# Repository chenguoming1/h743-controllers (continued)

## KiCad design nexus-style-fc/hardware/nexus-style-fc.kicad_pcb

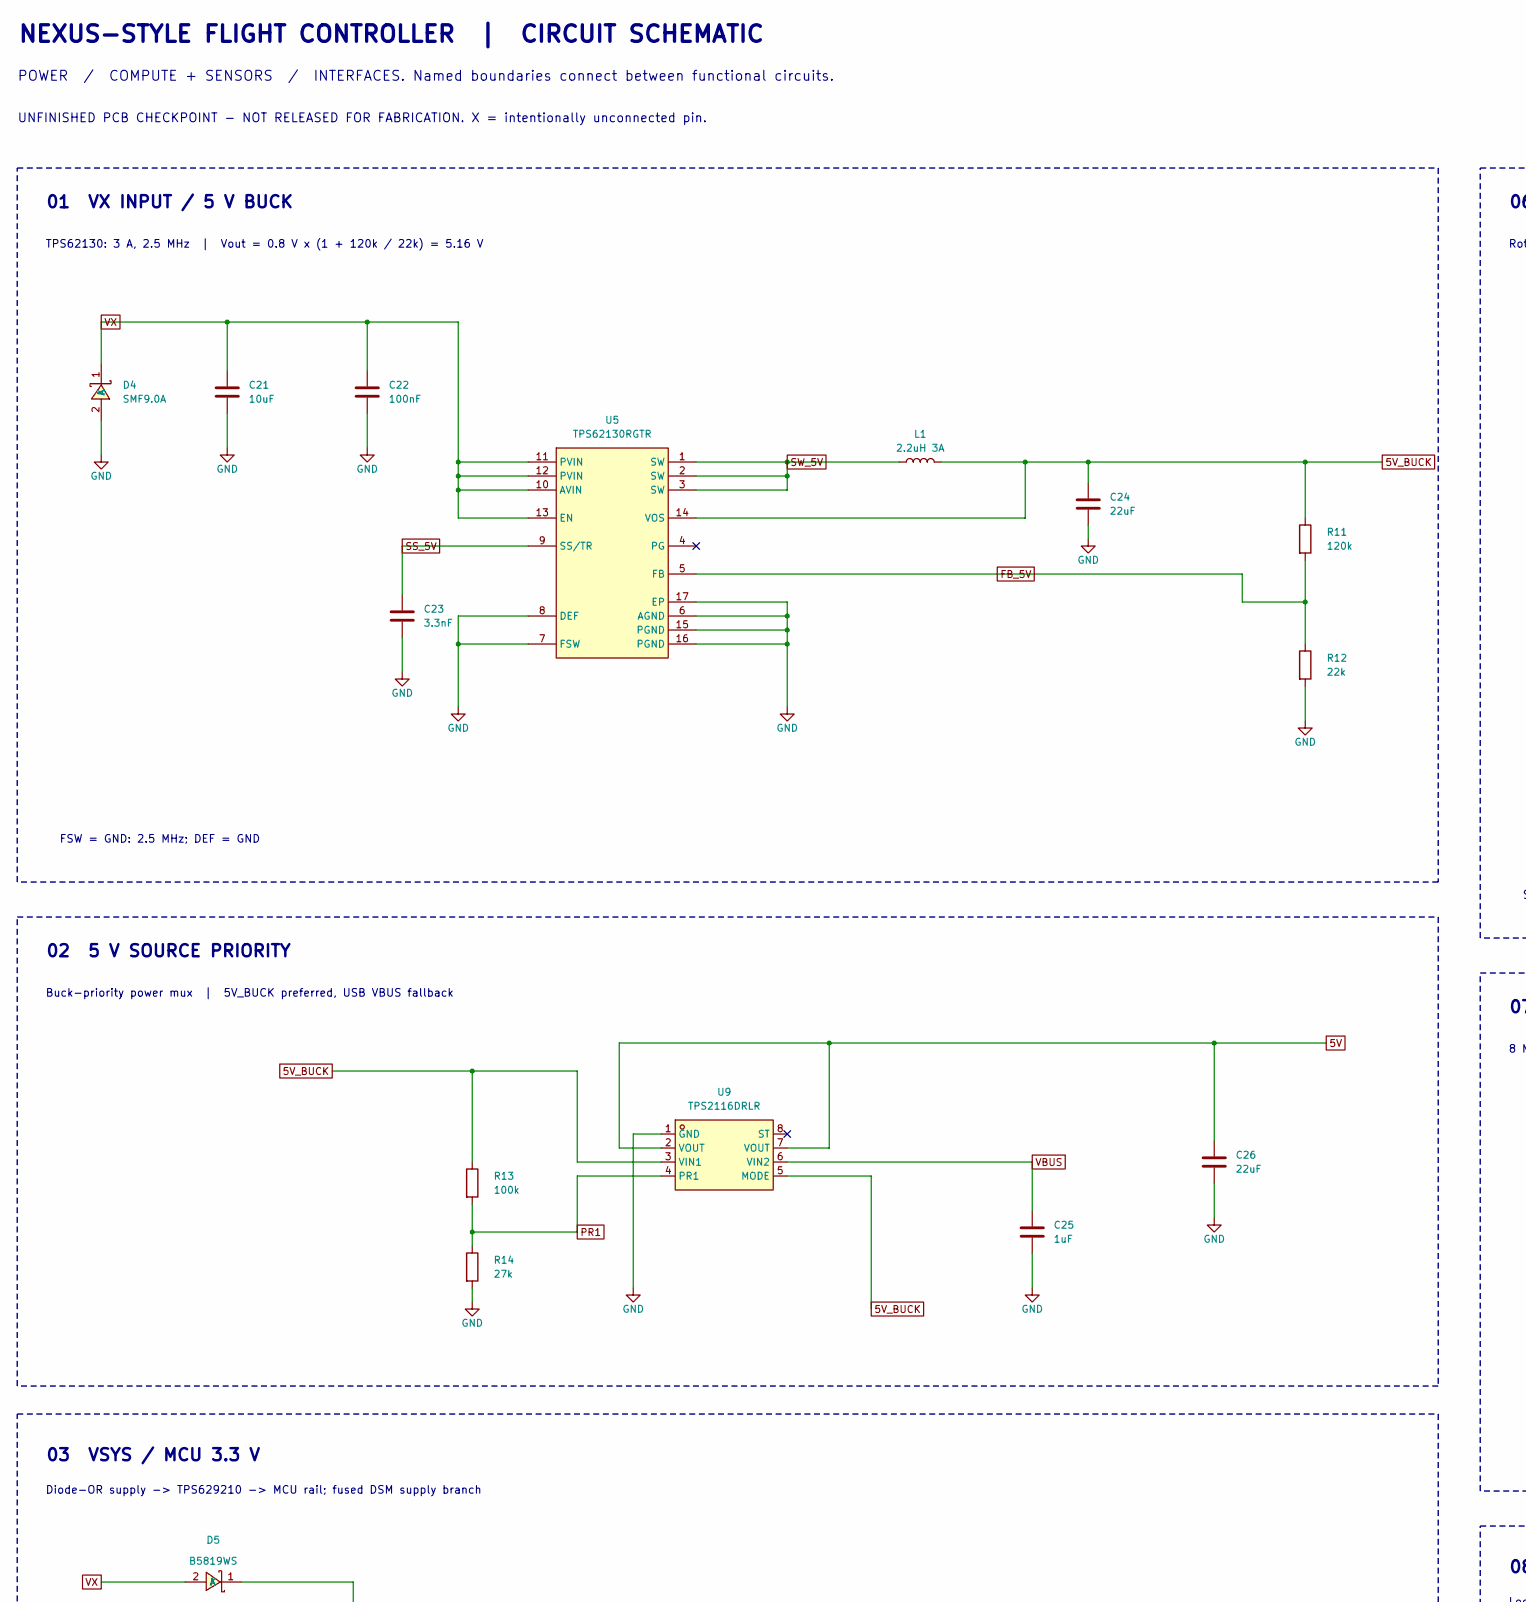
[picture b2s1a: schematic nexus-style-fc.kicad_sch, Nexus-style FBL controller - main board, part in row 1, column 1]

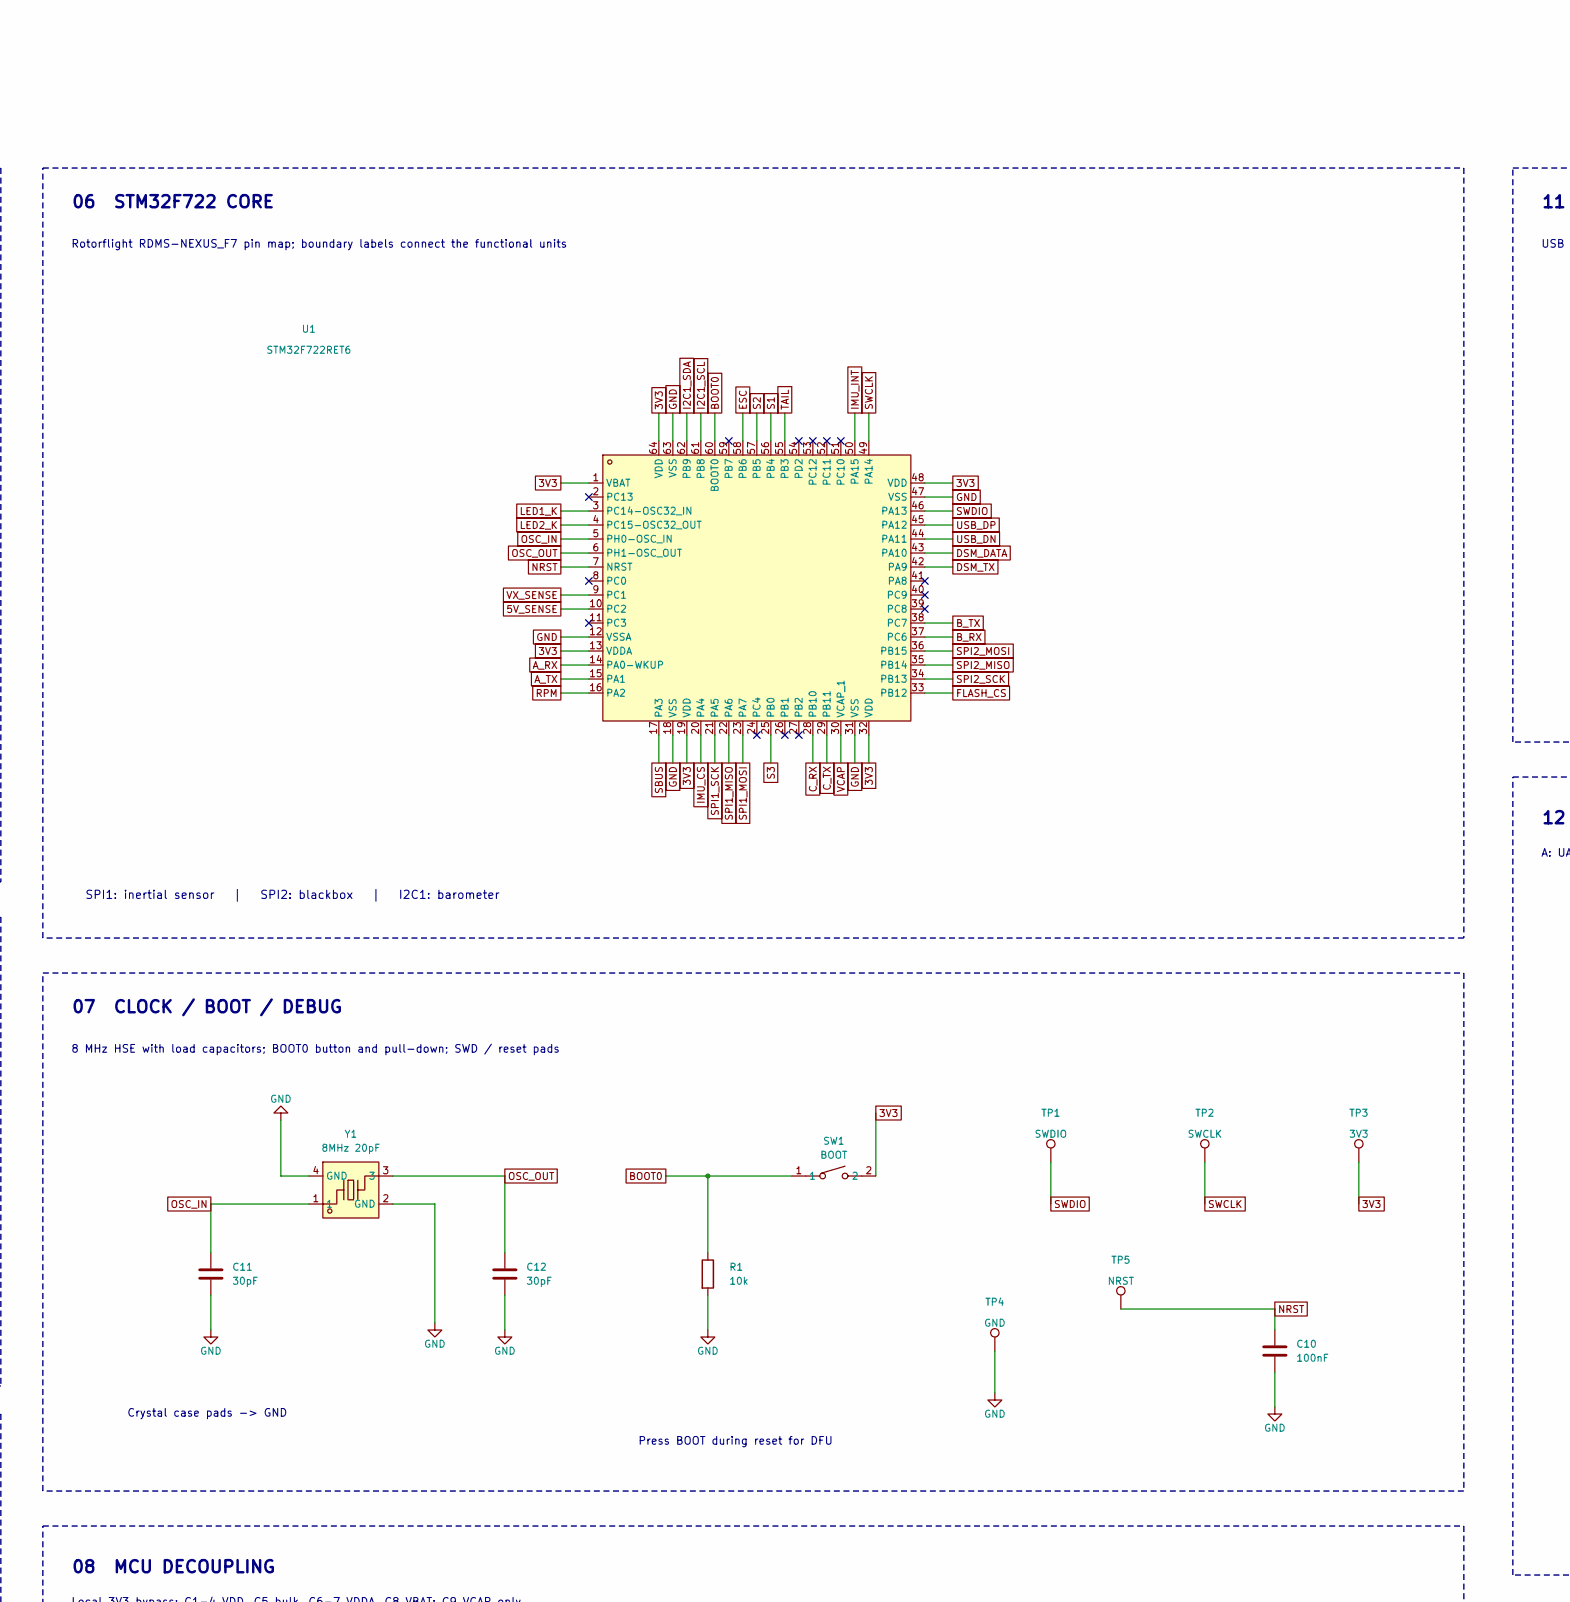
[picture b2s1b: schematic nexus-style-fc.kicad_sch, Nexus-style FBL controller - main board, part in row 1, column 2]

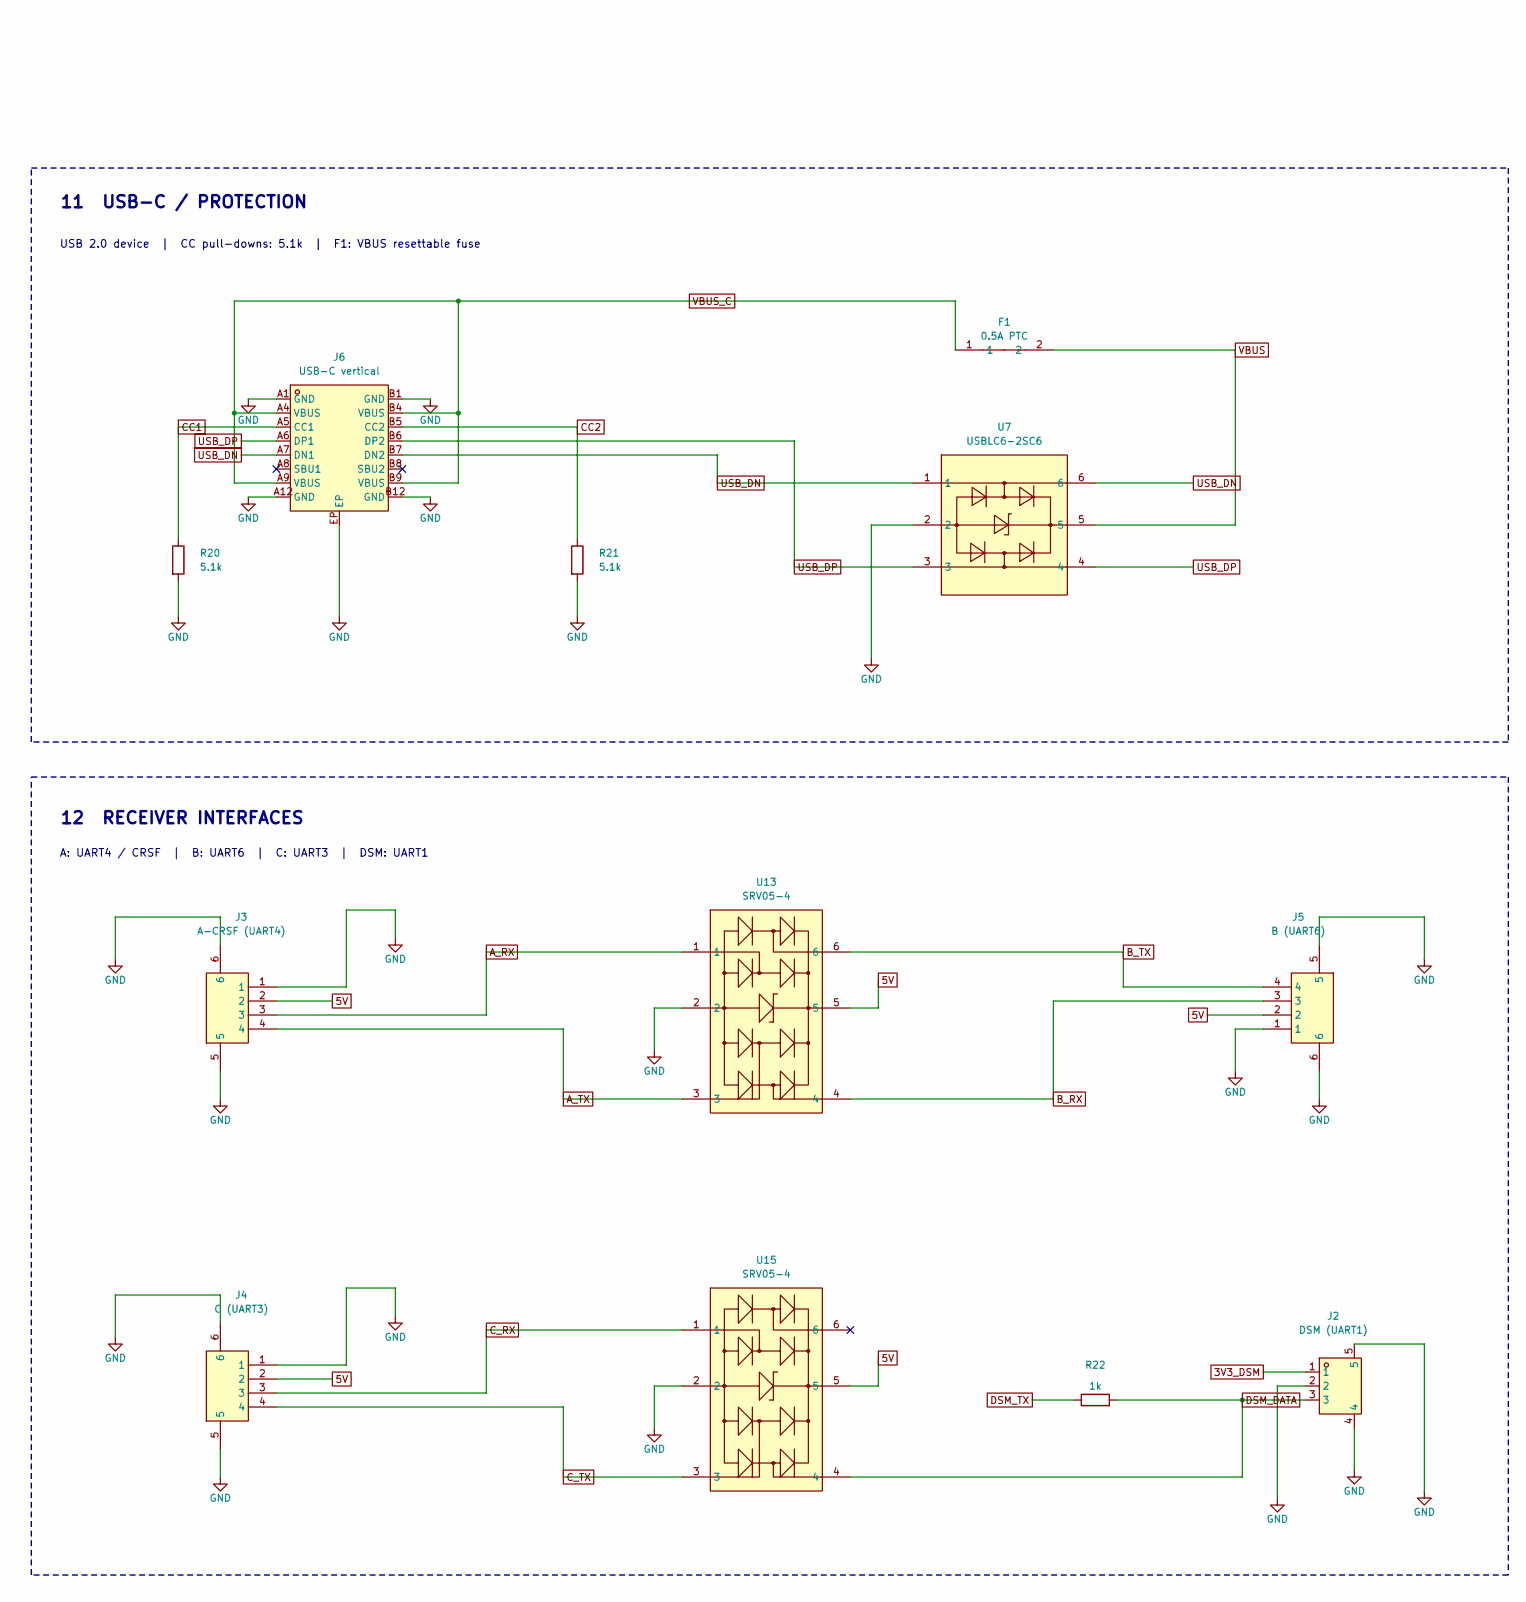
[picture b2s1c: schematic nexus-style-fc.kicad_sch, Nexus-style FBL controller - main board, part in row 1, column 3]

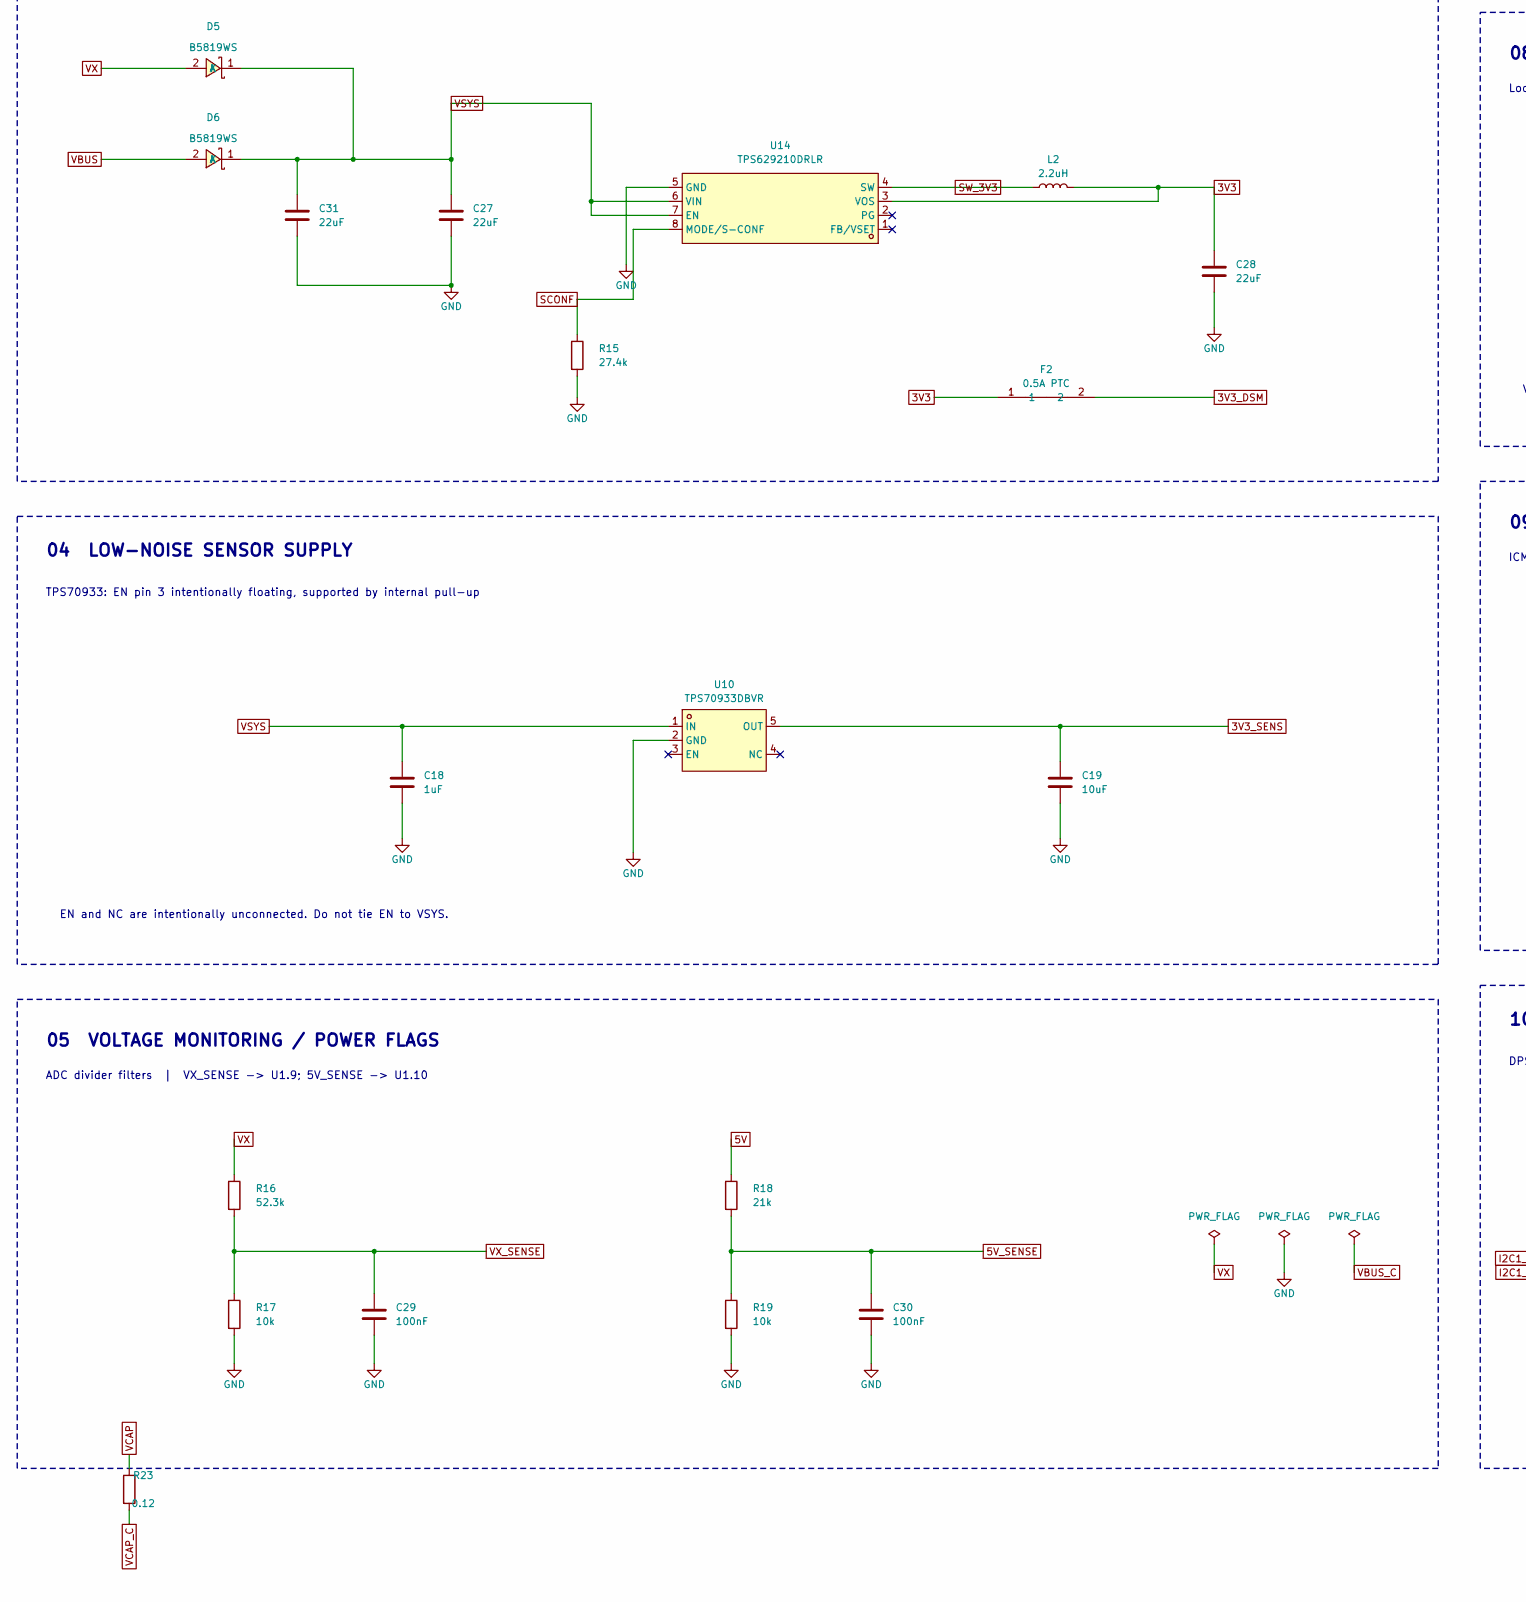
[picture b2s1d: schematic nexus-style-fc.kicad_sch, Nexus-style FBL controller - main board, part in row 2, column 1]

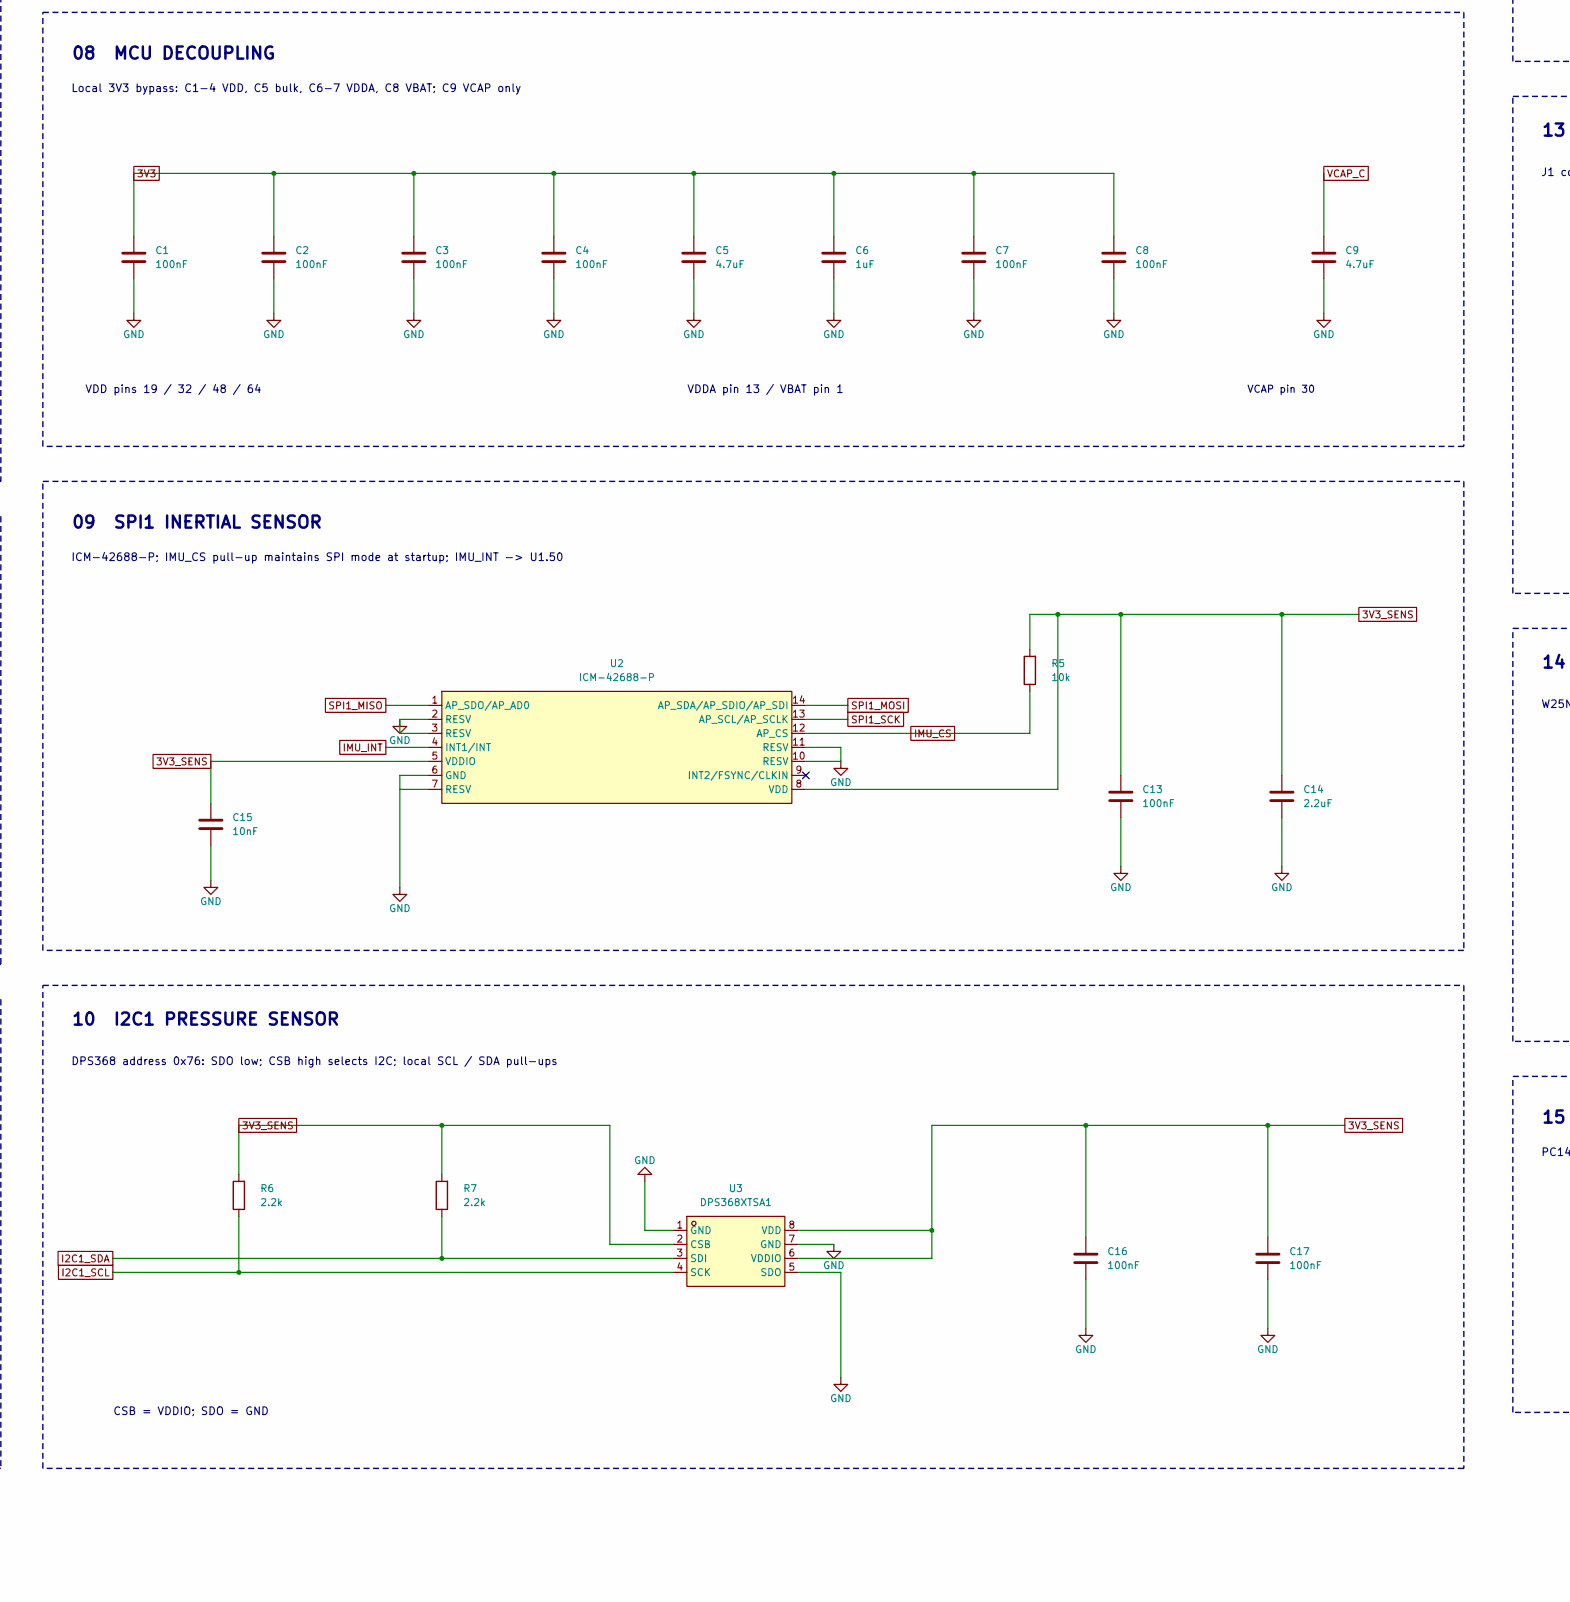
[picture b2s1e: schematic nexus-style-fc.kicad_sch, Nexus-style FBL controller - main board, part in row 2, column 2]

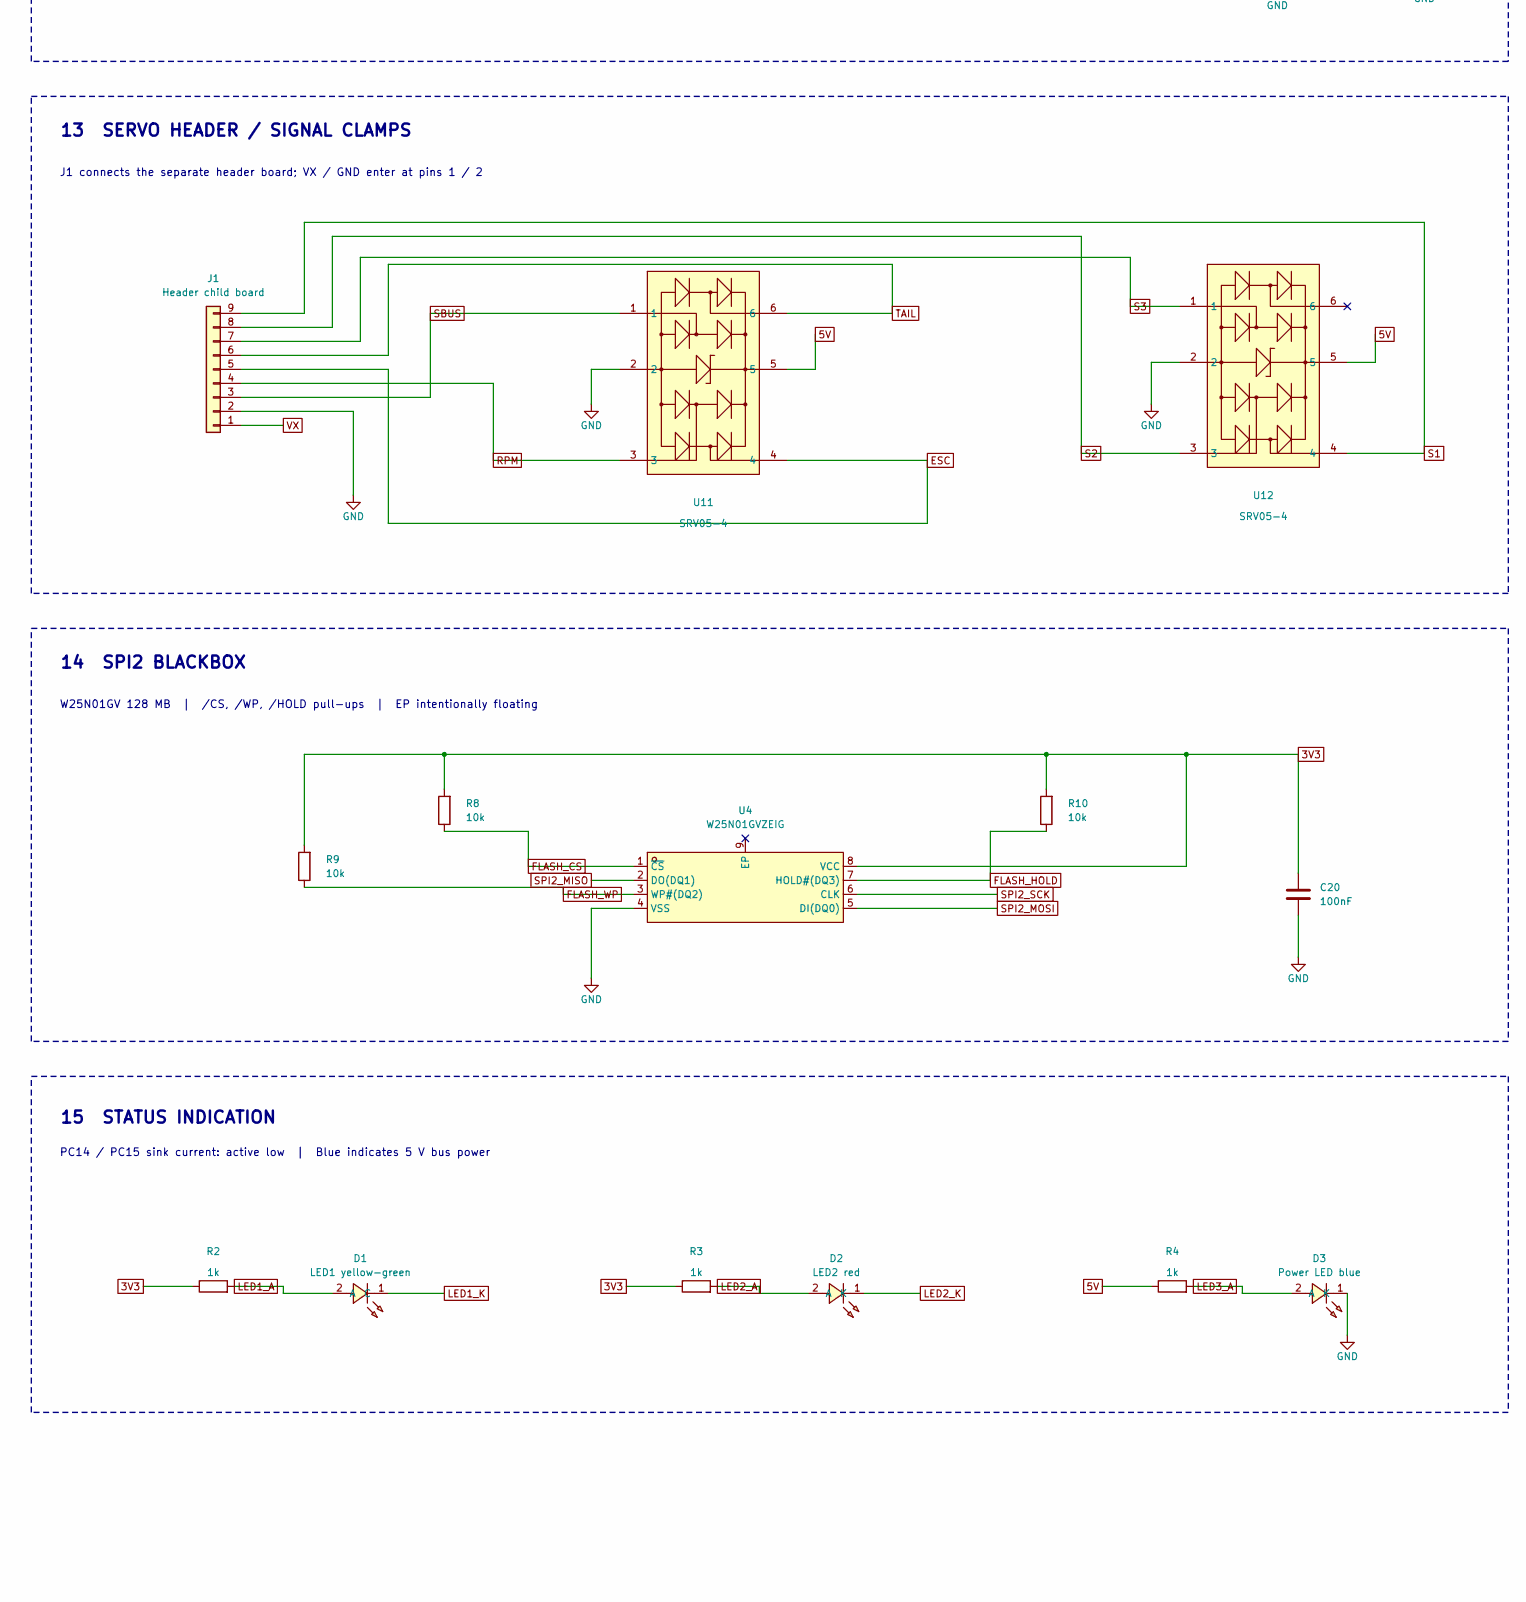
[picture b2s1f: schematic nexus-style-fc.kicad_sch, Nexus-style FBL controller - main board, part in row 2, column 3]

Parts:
C1, C2, C3, C4, C7, C8, C10, C13, C16, C17, C20, C22, C29, C30: 100nF; C_0402_1005Metric; LCSC C1525
C5: 4.7uF; C_0603_1608Metric; LCSC C69335
C6, C18, C25: 1uF; C_0402_1005Metric; LCSC C52923
C9: 4.7uF; C_0402_1005Metric__VCAP_Dense; LCSC C368809
C11, C12: 30pF; C_0402_1005Metric; LCSC C1570
C14: 2.2uF; C_0402_1005Metric; LCSC C12530
C15: 10nF; C_0402_1005Metric; LCSC C15195
C19: 10uF; C_0603_1608Metric; LCSC C19702
C21: 10uF; C_0603_1608Metric; LCSC C96446
C23: 3.3nF; C_0402_1005Metric; LCSC C26404
C24, C26: 22uF; C_0805_2012Metric; LCSC C602037
C27, C31: 22uF; C_0805_2012Metric_Samsung_CL21_MinLand; LCSC C602037
C28: 22uF; C_0603_1608Metric; LCSC C86295
D1: LED1 yellow-green; LED0603-RD_GREEN__NexusMain_D1; LCSC C965806
D2: LED2 red; LED0603-RD_RED__NexusMain_D2; LCSC C965799
D3: Power LED blue; LED0603-RD_BLUE__NexusMain_D3; LCSC C965807
D4: SMF9.0A; SOD-123FL_L2.8-W1.8-LS3.6-RD__Littelfuse_SMF9; LCSC C1973343
D5, D6: B5819WS; SOD-323_L1.8-W1.3-LS2.5-RD; LCSC C22624
F1: 0.5A PTC; F0805__NexusMain_F1; LCSC C20978
F2: 0.5A PTC; F0805__NexusMain_F2; LCSC C20978
J1: Header child board; HeaderBoard_Joint
J2: DSM (UART1); CONN-SMD_B3B-ZR-SM4-TF__NexusMain_J2; LCSC C489717
J3: A-CRSF (UART4); CONN-SMD_4P-P1.25_BM04B-GHS-TBT-LF-SN__NexusMain_J3; LCSC C161692
J4: C (UART3); CONN-SMD_4P-P1.25_BM04B-GHS-TBT-LF-SN__NexusMain_J4; LCSC C161692
J5: B (UART6); CONN-SMD_4P-P1.25_BM04B-GHS-TBT-LF-SN__NexusMain_J5; LCSC C161692
J6: USB-C vertical; USB-C-SMD_TYPE-C-31-D-06__NexusMain_J6; LCSC C2689964
L1: 2.2uH 3A; IND-SMD_L4.6-W4.1; LCSC C142096
L2: 2.2uH; IND-SMD_L2.0-W1.6__NexusMain_L2; LCSC C5291913
R1, R5, R8, R9, R10, R17, R19: 10k; R_0402_1005Metric; LCSC C25744
R2: 1k; R_0402_1005Metric__NexusMain_R2; LCSC C11702
R3, R22: 1k; R_0402_1005Metric; LCSC C11702
R4: 1k; R_0402_1005Metric__NexusMain_R4; LCSC C11702
R6, R7: 2.2k; R_0402_1005Metric; LCSC C25879
R11: 120k; R_0402_1005Metric; LCSC C25750
R12: 22k; R_0402_1005Metric; LCSC C25768
R13: 100k; R_0402_1005Metric; LCSC C25741
R14: 27k; R_0402_1005Metric; LCSC C25771
R15: 27.4k; R_0402_1005Metric; LCSC C26971
R16: 52.3k; R_0402_1005Metric; LCSC C26982
R18: 21k; R_0402_1005Metric; LCSC C25766
R20, R21: 5.1k; R_0402_1005Metric; LCSC C25905
R23: 0.12; R_0402_1005Metric__VCAP_Dense; LCSC C2766886
SW1: BOOT; SW-SMD_L3.9-W3.0-P4.45; LCSC C720477
TP1: SWDIO; TestPoint_Pad_D1.0mm
TP2: SWCLK; TestPoint_Pad_D1.0mm
TP3: 3V3; TestPoint_Pad_D1.0mm
TP4: GND; TestPoint_Pad_D1.0mm
TP5: NRST; TestPoint_Pad_D1.0mm
U1: STM32F722RET6; LQFP-64_L10.0-W10.0-P0.50-LS12.0-BL; LCSC C118207
U2: ICM-42688-P; LGA-14_L3.0-W2.5-P0.50-TL; LCSC C1850418
U3: DPS368XTSA1; LGA-8_L2.5-W2.0-P0.65-TR_DPS368; LCSC C3232508
U4: W25N01GVZEIG; WSON-8_L8.0-W6.10-P1.27-BL-EP; LCSC C907680
U5: TPS62130RGTR; QFN-16_L3.0-W3.0-P0.50-TL-EP1.7; LCSC C43590
U7: USBLC6-2SC6; SOT-23-6_L2.9-W1.6-P0.95-LS2.8-BL; LCSC C7519
U9: TPS2116DRLR; SOT-583-8_L2.1-W1.6-P0.50-LS1.6-BL; LCSC C3235557
U10: TPS70933DBVR; TPS70933DBVR_TI_DBV0005A; LCSC C89347
U11, U12, U13, U15: SRV05-4; SOT-23-6_L2.9-W1.6-P0.95-LS2.8-BR; LCSC C13612
U14: TPS629210DRLR; SOT-5X3-8_L2.1-W1.2-P0.50-LS1.6-BL_DRL0008A; LCSC C5219301
Y1: 8MHz 20pF; CRYSTAL-SMD_4P-L3.2-W2.5-BL__NexusMain_Y1; LCSC C5181477

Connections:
3V3: C1.1, C2.1, C3.1, C4.1, C5.1, C6.1, C7.1, C8.1, C20.1, C28.1, F2.1, L2.2, R2.1, R3.1, R8.2, R9.2, R10.2, SW1.2, TP3.1, U1.1 (VBAT), U1.13 (VDDA), U1.19 (VDD), U1.32 (VDD), U1.48 (VDD), U1.64 (VDD), U4.8 (VCC), U14.3 (VOS)
3V3_DSM: F2.2, J2.1
3V3_SENS: C13.1, C14.1, C15.1, C16.1, C17.1, C19.1, R5.2, R6.2, R7.2, U2.5 (VDDIO), U2.8 (VDD), U3.2 (CSB), U3.6 (VDDIO), U3.8 (VDD), U10.5 (OUT)
5V: C26.1, J3.2, J4.2, J5.2, R4.1, R18.1, U9.2 (VOUT), U9.7 (VOUT), U11.5, U12.5, U13.5, U15.5
5V_BUCK: C24.1, L1.2, R11.1, R13.1, U5.14 (VOS), U9.3 (VIN1), U9.5 (MODE)
5V_SENSE: C30.1, R18.2, R19.1, U1.10 (PC2)
A_RX: J3.3, U1.14 (PA0-WKUP), U13.1
A_TX: J3.4, U1.15 (PA1), U13.3
BOOT0: R1.1, SW1.1, U1.60 (BOOT0)
B_RX: J5.3, U1.37 (PC6), U13.4
B_TX: J5.4, U1.38 (PC7), U13.6
CC1: J6.A5 (CC1), R20.1
CC2: J6.B5 (CC2), R21.1
C_RX: J4.3, U1.28 (PB10), U15.1
C_TX: J4.4, U1.29 (PB11), U15.3
DSM_DATA: J2.3, R22.2, U1.43 (PA10), U15.4
DSM_TX: R22.1, U1.42 (PA9)
ESC: J1.5, U1.58 (PB6), U11.4
FB_5V: R11.2, R12.1, U5.5 (FB)
FLASH_CS: R8.1, U1.33 (PB12), U4.1 (~CS)
FLASH_HOLD: R10.1, U4.7 (HOLD#(DQ3))
FLASH_WP: R9.1, U4.3 (WP#(DQ2))
GND: C1.2, C2.2, C3.2, C4.2, C5.2, C6.2, C7.2, C8.2, C9.2, C10.2, C11.2, C12.2, C13.2, C14.2, C15.2, C16.2, C17.2, C18.2, C19.2, C20.2, C21.2, C22.2, C23.2, C24.2, C25.2, C26.2, C27.2, C28.2, C29.2, C30.2, C31.2, D3.1 (K), D4.2 (A), J1.2, J2.2, J2.4, J2.5, J3.1, J3.5, J3.6, J4.1, J4.5, J4.6, J5.1, J5.5, J5.6, J6.A1 (GND), J6.A12 (GND), J6.B1 (GND), J6.B12 (GND), J6.EP, R1.2, R12.2, R14.2, R15.2, R17.2, R19.2, R20.2, R21.2, TP4.1, U1.12 (VSSA), U1.18 (VSS), U1.31 (VSS), U1.47 (VSS), U1.63 (VSS), U2.2 (RESV), U2.3 (RESV), U2.6 (GND), U2.7 (RESV), U2.10 (RESV), U2.11 (RESV), U3.1 (GND), U3.5 (SDO), U3.7 (GND), U4.4 (VSS), U5.6 (AGND), U5.7 (FSW), U5.8 (DEF), U5.15 (PGND), U5.16 (PGND), U5.17 (EP), U7.2, U9.1 (GND), U10.2 (GND), U11.2, U12.2, U13.2, U14.5 (GND), U15.2, Y1.2 (GND), Y1.4 (GND)
I2C1_SCL: R6.1, U1.61 (PB8), U3.4 (SCK)
I2C1_SDA: R7.1, U1.62 (PB9), U3.3 (SDI)
IMU_CS: R5.1, U1.20 (PA4), U2.12 (AP_CS)
IMU_INT: U1.50 (PA15), U2.4 (INT1/INT)
LED1_A: D1.2 (A), R2.2
LED1_K: D1.1 (C), U1.3 (PC14-OSC32_IN)
LED2_A: D2.2 (A), R3.2
LED2_K: D2.1 (K), U1.4 (PC15-OSC32_OUT)
LED3_A: D3.2 (A), R4.2
NRST: C10.1, TP5.1, U1.7 (NRST)
OSC_IN: C11.1, U1.5 (PH0-OSC_IN), Y1.1
OSC_OUT: C12.1, U1.6 (PH1-OSC_OUT), Y1.3
PR1: R13.2, R14.1, U9.4 (PR1)
RPM: J1.4, U1.16 (PA2), U11.3
S1: J1.9, U1.56 (PB4), U12.4
S2: J1.8, U1.57 (PB5), U12.3
S3: J1.7, U1.25 (PB0), U12.1
SBUS: J1.3, U1.17 (PA3), U11.1
SCONF: R15.1, U14.8 (MODE/S-CONF)
SPI1_MISO: U1.22 (PA6), U2.1 (AP_SDO/AP_AD0)
SPI1_MOSI: U1.23 (PA7), U2.14 (AP_SDA/AP_SDIO/AP_SDI)
SPI1_SCK: U1.21 (PA5), U2.13 (AP_SCL/AP_SCLK)
SPI2_MISO: U1.35 (PB14), U4.2 (DO(DQ1))
SPI2_MOSI: U1.36 (PB15), U4.5 (DI(DQ0))
SPI2_SCK: U1.34 (PB13), U4.6 (CLK)
SS_5V: C23.1, U5.9 (SS/TR)
SWCLK: TP2.1, U1.49 (PA14)
SWDIO: TP1.1, U1.46 (PA13)
SW_3V3: L2.1, U14.4 (SW)
SW_5V: L1.1, U5.1 (SW), U5.2 (SW), U5.3 (SW)
TAIL: J1.6, U1.55 (PB3), U11.6
USB_DN: J6.A7 (DN1), J6.B7 (DN2), U1.44 (PA11), U7.1, U7.6
USB_DP: J6.A6 (DP1), J6.B6 (DP2), U1.45 (PA12), U7.3, U7.4
VBUS: C25.1, D6.2 (A), F1.2, U7.5, U9.6 (VIN2)
VBUS_C: F1.1, J6.A4 (VBUS), J6.A9 (VBUS), J6.B4 (VBUS), J6.B9 (VBUS)
VCAP: R23.1, U1.30 (VCAP_1)
VCAP_C: C9.1, R23.2
VSYS: C18.1, C27.1, C31.1, D5.1 (K), D6.1 (K), U10.1 (IN), U14.6 (VIN), U14.7 (EN)
VX: C21.1, C22.1, D4.1 (K), D5.2 (A), J1.1, R16.1, U5.10 (AVIN), U5.11 (PVIN), U5.12 (PVIN), U5.13 (EN)
VX_SENSE: C29.1, R16.2, R17.1, U1.9 (PC1)

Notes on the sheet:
8 MHz HSE with load capacitors; BOOT0 button and pull-down; SWD / reset pads
10 I2C1 PRESSURE SENSOR
09 SPI1 INERTIAL SENSOR
TPS62130: 3 A, 2.5 MHz | Vout = 0.8 V x (1 + 120k / 22k) = 5.16 V
VDD pins 19 / 32 / 48 / 64
USB 2.0 device | CC pull-downs: 5.1k | F1: VBUS resettable fuse
06 STM32F722 CORE
ADC divider filters | VX_SENSE -> U1.9; 5V_SENSE -> U1.10
Buck-priority power mux | 5V_BUCK preferred, USB VBUS fallback
DPS368 address 0x76: SDO low; CSB high selects I2C; local SCL / SDA pull-ups
POWER / COMPUTE + SENSORS / INTERFACES. Named boundaries connect between functional circuits.
15 STATUS INDICATION
SPI1: inertial sensor | SPI2: blackbox | I2C1: barometer
ICM-42688-P; IMU_CS pull-up maintains SPI mode at startup; IMU_INT -> U1.50
VDDA pin 13 / VBAT pin 1
04 LOW-NOISE SENSOR SUPPLY
NEXUS-STYLE FLIGHT CONTROLLER | CIRCUIT SCHEMATIC
Crystal case pads -> GND
02 5 V SOURCE PRIORITY
Local 3V3 bypass: C1-4 VDD, C5 bulk, C6-7 VDDA, C8 VBAT; C9 VCAP only
FSW = GND: 2.5 MHz; DEF = GND
W25N01GV 128 MB | /CS, /WP, /HOLD pull-ups | EP intentionally floating
Diode-OR supply -> TPS629210 -> MCU rail; fused DSM supply branch
05 VOLTAGE MONITORING / POWER FLAGS
Rotorflight RDMS-NEXUS_F7 pin map; boundary labels connect the functional units
J1 connects the separate header board; VX / GND enter at pins 1 / 2
13 SERVO HEADER / SIGNAL CLAMPS
01 VX INPUT / 5 V BUCK
UNFINISHED PCB CHECKPOINT - NOT RELEASED FOR FABRICATION. X = intentionally unconnected pin.
03 VSYS / MCU 3.3 V
Press BOOT during reset for DFU
11 USB-C / PROTECTION
A: UART4 / CRSF | B: UART6 | C: UART3 | DSM: UART1
CSB = VDDIO; SDO = GND
07 CLOCK / BOOT / DEBUG
08 MCU DECOUPLING
VCAP pin 30
TPS70933: EN pin 3 intentionally floating, supported by internal pull-up
PC14 / PC15 sink current: active low | Blue indicates 5 V bus power
12 RECEIVER INTERFACES

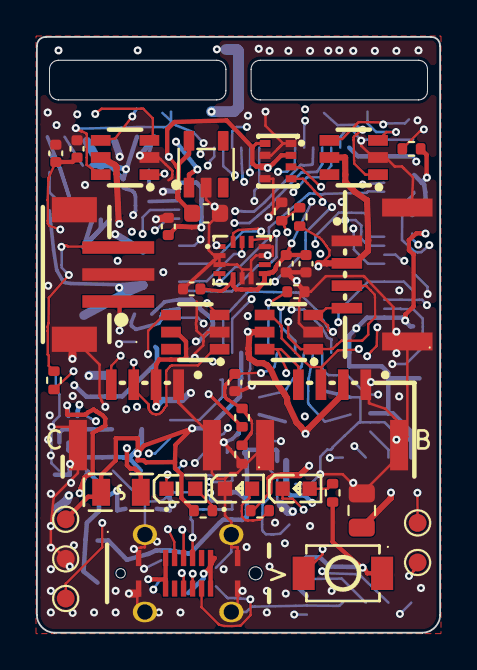
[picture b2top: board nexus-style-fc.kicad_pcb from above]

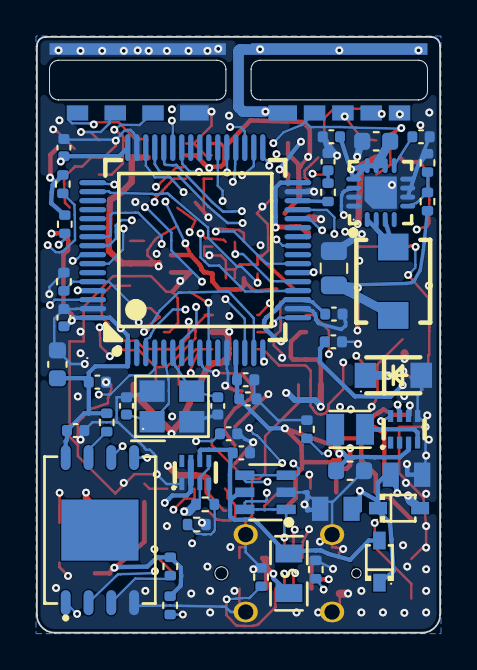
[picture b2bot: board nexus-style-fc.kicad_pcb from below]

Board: 6 copper layers, 22.4 x 33.1 mm, 90 parts (48 on the bottom side), 63 nets.

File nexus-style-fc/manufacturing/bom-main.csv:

"Designator","Value","Footprint","LCSC Part #","Quantity"
"C1-C4,C7,C8,C10,C13,C16,C17,C20,C22,C29,C30","100nF","Capacitor_SMD:C_0402_1005Metric","C1525","14"
"C5,C9,C27","4.7uF","Capacitor_SMD:C_0603_1608Metric","C69335","3"
"C6,C18,C25","1uF","Capacitor_SMD:C_0402_1005Metric","C52923","3"
"C11,C12","30pF","Capacitor_SMD:C_0402_1005Metric","C1570","2"
"C14","2.2uF","Capacitor_SMD:C_0402_1005Metric","C12530","1"
"C15","10nF","Capacitor_SMD:C_0402_1005Metric","C15195","1"
"C19","10uF","Capacitor_SMD:C_0603_1608Metric","C19702","1"
"C21","10uF","Capacitor_SMD:C_0603_1608Metric","C96446","1"
"C23","3.3nF","Capacitor_SMD:C_0402_1005Metric","C26404","1"
"C24,C26","22uF","Capacitor_SMD:C_0805_2012Metric","C602037","2"
"C28","22uF","Capacitor_SMD:C_0603_1608Metric","C86295","1"
"D1","LED1 yellow-green","NexusFC:LED0603-RD_GREEN","C965806","1"
"D2","LED2 red","NexusFC:LED0603-RD_RED","C965799","1"
"D3","Power LED blue","NexusFC:LED0603-RD_BLUE","C965807","1"
"D4","SMF13A","NexusFC:SOD-123FL_L2.8-W1.8-LS3.6-RD","C353315","1"
"D5,D6","B5819WS","NexusFC:SOD-323_L1.8-W1.3-LS2.5-RD","C22624","2"
"F1,F2","0.5A PTC","NexusFC:F0805","C20978","2"
"J1","Header child board","NexusFC:HeaderBoard_Joint","","1"
"J2","DSM (UART1)","NexusFC:CONN-SMD_B3B-ZR-SM4-TF","C489717","1"
"J3","A-CRSF (UART4)","NexusFC:CONN-SMD_4P-P1.25_BM04B-GHS-TBT-LF-SN","C161692","1"
"J4","C (UART3)","NexusFC:CONN-SMD_4P-P1.25_BM04B-GHS-TBT-LF-SN","C161692","1"
"J5","B (UART6)","NexusFC:CONN-SMD_4P-P1.25_BM04B-GHS-TBT-LF-SN","C161692","1"
"J6","USB-C vertical","NexusFC:USB-C-SMD_TYPE-C-31-D-06","C2689964","1"
"L1","2.2uH 3A","NexusFC:IND-SMD_L4.6-W4.1","C142096","1"
"L2","2.2uH","NexusFC:IND-SMD_L2.0-W1.6","C5291913","1"
"R1,R5,R8-R10,R17,R19","10k","Resistor_SMD:R_0402_1005Metric","C25744","7"
"R2-R4,R22","1k","Resistor_SMD:R_0402_1005Metric","C11702","4"
"R6,R7","2.2k","Resistor_SMD:R_0402_1005Metric","C25879","2"
"R11","120k","Resistor_SMD:R_0402_1005Metric","C25750","1"
"R12","22k","Resistor_SMD:R_0402_1005Metric","C25768","1"
"R13","100k","Resistor_SMD:R_0402_1005Metric","C25741","1"
"R14","27k","Resistor_SMD:R_0402_1005Metric","C25771","1"
"R15","27.4k","Resistor_SMD:R_0402_1005Metric","C26971","1"
"R16","52.3k","Resistor_SMD:R_0402_1005Metric","C26982","1"
"R18","21k","Resistor_SMD:R_0402_1005Metric","C25766","1"
"R20,R21","5.1k","Resistor_SMD:R_0402_1005Metric","C25905","2"
"SW1","BOOT","NexusFC:SW-SMD_L3.9-W3.0-P4.45","C720477","1"
"U1","STM32F722RET6","NexusFC:LQFP-64_L10.0-W10.0-P0.50-LS12.0-BL","C118207","1"
"U2","ICM-42688-P","NexusFC:LGA-14_L3.0-W2.5-P0.50-TL","C1850418","1"
"U3","DPS368XTSA1","NexusFC:LGA-8_L2.5-W2.0-P0.65-TR_DPS368","C3232508","1"
"U4","W25N01GVZEIG","NexusFC:WSON-8_L8.0-W6.10-P1.27-BL-EP","C907680","1"
"U5","TPS62130RGTR","NexusFC:QFN-16_L3.0-W3.0-P0.50-TL-EP1.7","C43590","1"
"U7","USBLC6-2SC6","NexusFC:SOT-23-6_L2.9-W1.6-P0.95-LS2.8-BL","C7519","1"
"U9","TPS2116DRLR","NexusFC:SOT-583-8_L2.1-W1.6-P0.50-LS1.6-BL","C3235557","1"
"U10","TPS70933DBVR","NexusFC:SOT-23-5_L3.0-W1.7-P0.95-LS2.8-BL","C89347","1"
"U11-U13,U15","SRV05-4","NexusFC:SOT-23-6_L2.9-W1.6-P0.95-LS2.8-BR","C13612","4"
"U14","TPS629210DRLR","NexusFC:SOT-5X3-8_L2.1-W1.2-P0.50-LS1.6-BL_DRL0008A","C5219301","1"
"Y1","8MHz 20pF","NexusFC:CRYSTAL-SMD_4P-L3.2-W2.5-BL","C5181477","1"
